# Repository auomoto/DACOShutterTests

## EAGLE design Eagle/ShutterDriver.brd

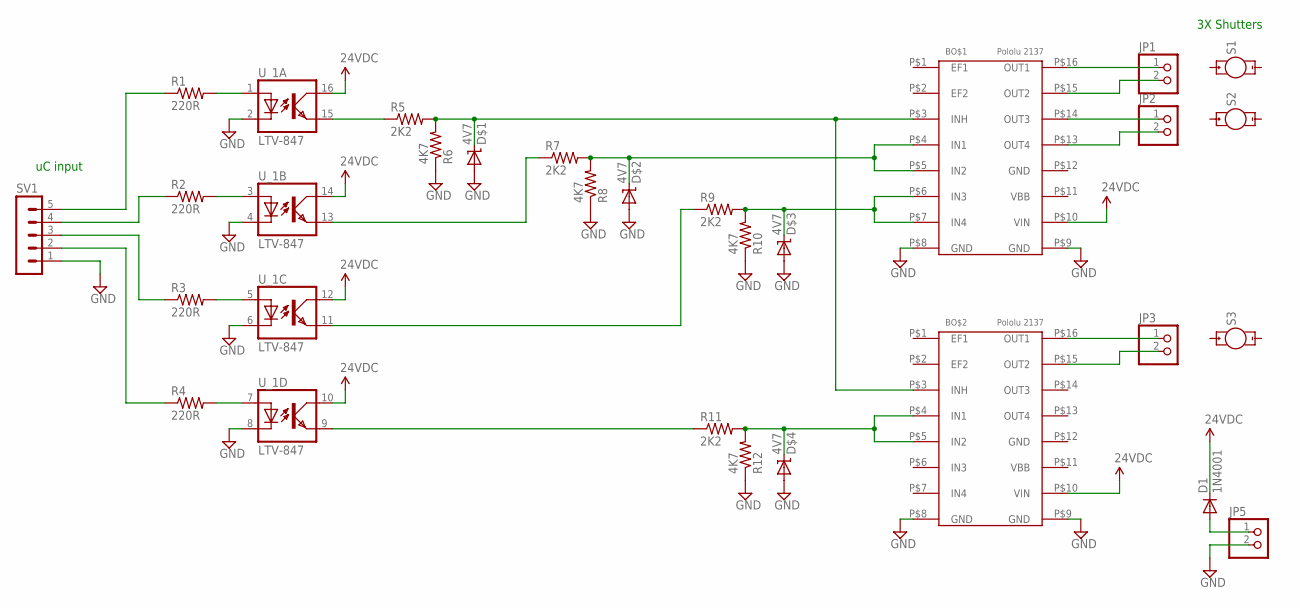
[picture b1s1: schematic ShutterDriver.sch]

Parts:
BO$1, BO$2: Pololu 2137; POLOLU2137
D1: 1N4001; DO41-10
D$1, D$2, D$3, D$4: 4V7; DIODE-ZENER
JP1, JP2, JP3, JP5: PINHD-1X2; 1X02
R1, R2, R3, R4: 220R; AXIAL-0.3
R5, R7, R9, R11: 2K2; AXIAL-0.3
R6, R8, R10, R12: 4K7; AXIAL-0.3
S1, S2, S3: MOTOR10MM; VIBE-MOTOR-10MM
SV1: MA05-1
U_1: LTV-847; DIL16

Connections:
GND: BO$1.P$8 (GND), BO$1.P$9 (GND), BO$1.P$12 (GND), BO$2.P$8 (GND), BO$2.P$9 (GND), BO$2.P$12 (GND), D$1.P$2 (A), D$2.P$2 (A), D$3.P$2 (A), D$4.P$2 (A), JP5.2, R6.P$1 (1), R8.P$1 (1), R10.P$1 (1), R12.P$1 (1), U_1.2 (C), U_1.4 (C), U_1.6 (C), U_1.8 (C)
INHIBIT1: BO$1.P$3 (INH), BO$2.P$3 (INH), D$1.P$1 (C), R5.P$2 (2), R6.P$2 (2)
INHIBIT2: BO$1.P$4 (IN1), BO$1.P$5 (IN2), D$2.P$1 (C), R7.P$2 (2), R8.P$2 (2)
INHIBIT3: BO$1.P$6 (IN3), BO$1.P$7 (IN4), D$3.P$1 (C), R9.P$2 (2), R10.P$2 (2)
INHIBIT4: BO$2.P$4 (IN1), BO$2.P$5 (IN2), D$4.P$1 (C), R11.P$2 (2), R12.P$2 (2)
unnamed: BO$1.P$16 (OUT1), JP1.1
unnamed: BO$1.P$15 (OUT2), JP1.2
unnamed: R5.P$1 (1), U_1.15 (EMIT)
unnamed: R7.P$1 (1), U_1.13 (EMIT)
unnamed: R9.P$1 (1), U_1.11 (EMIT)
unnamed: R11.P$1 (1), U_1.9 (EMIT)
unnamed: R1.P$2 (2), U_1.1 (A)
unnamed: R2.P$2 (2), U_1.3 (A)
unnamed: R3.P$2 (2), U_1.5 (A)
unnamed: R4.P$2 (2), U_1.7 (A)
unnamed: BO$1.P$14 (OUT3), JP2.1
unnamed: BO$1.P$13 (OUT4), JP2.2
unnamed: BO$2.P$16 (OUT1), JP3.1
unnamed: BO$2.P$15 (OUT2), JP3.2
unnamed: D1.A, JP5.1
unnamed: R1.P$1 (1), SV1.5
unnamed: R2.P$1 (1), SV1.4
unnamed: R3.P$1 (1), SV1.3
unnamed: R4.P$1 (1), SV1.2
VBB: BO$1.P$11 (VBB), BO$2.P$11 (VBB)
VCC: BO$1.P$10 (VIN), BO$2.P$10 (VIN), D1.C, U_1.10 (COL), U_1.12 (COL), U_1.14 (COL), U_1.16 (COL)

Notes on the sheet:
uC input
3X Shutters

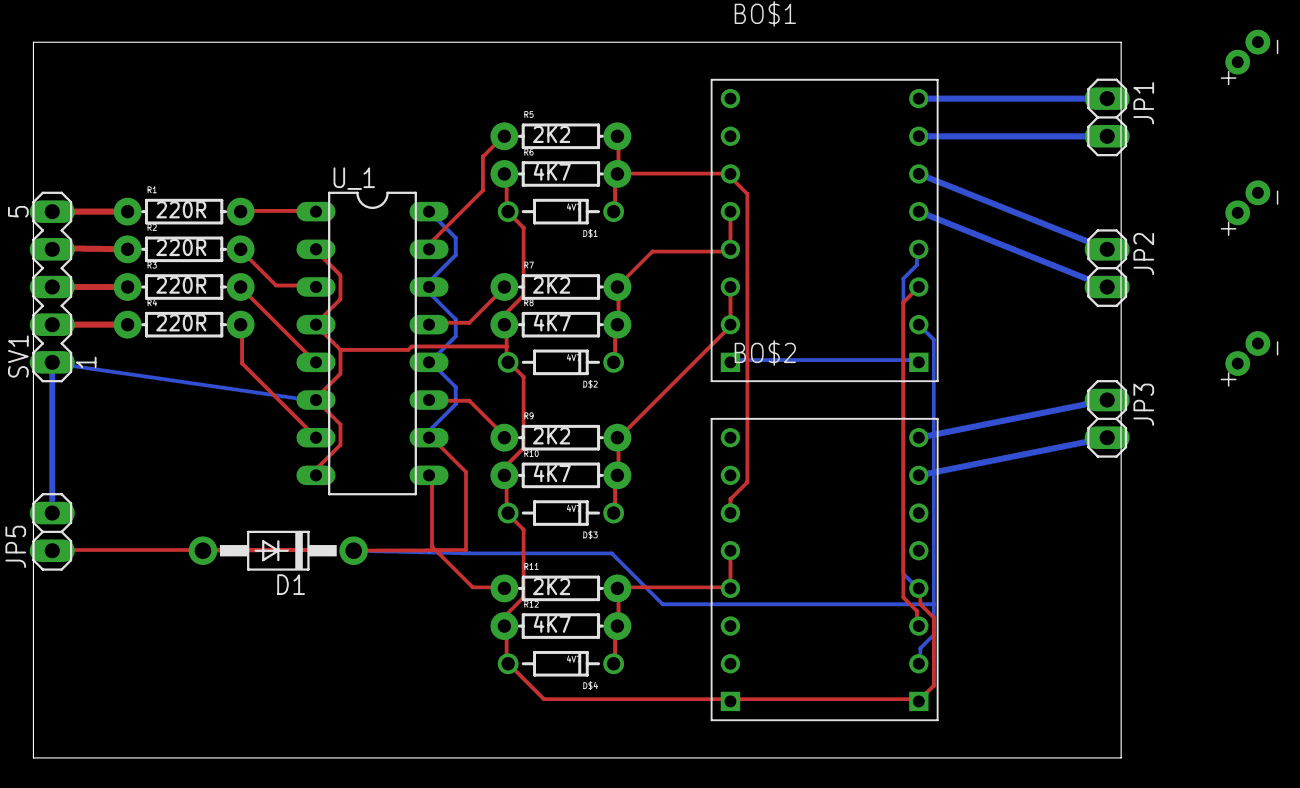
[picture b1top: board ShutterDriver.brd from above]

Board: 2 copper layers, 73.3 x 48.2 mm, 28 parts (0 on the bottom side), 26 nets.

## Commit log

2016-01-07 Delete

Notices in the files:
parts and their libraries:
SparkFun-DiscreteSemi: Licensing: CC v3.0 Share-Alike You are welcome to use this library for commercial purposes.
